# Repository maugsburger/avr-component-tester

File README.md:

avr-component-tester
====================

Board zu http://www.mikrocontroller.net/articles/AVR_Transistortester

* Schaltplan: https://raw.github.com/maugsburger/avr-component-tester/master/tester_sheet1.png
* Platinenvorderseite: https://raw.github.com/maugsburger/avr-component-tester/master/tester_top.png
* Platinenrückseite: https://raw.github.com/maugsburger/avr-component-tester/master/tester_bot.png
* Bauteilliste: https://raw.github.com/maugsburger/avr-component-tester/master/bom.txt

## Features

* Zweiter Spannungsregler für unsaubere Verbraucher
    * DC/DC-Wandler für Zenerdiodentest bis 30V
    * PWM-geregelte LCD-Hintergrundbeleuchtung

* Passt in Strapubox 6000

## Lizenz
<br />This work is licensed under a <a rel="license" href="http://creativecommons.org/licenses/by-sa/4.0/">Creative Commons Attribution-ShareAlike 4.0 International License</a>.

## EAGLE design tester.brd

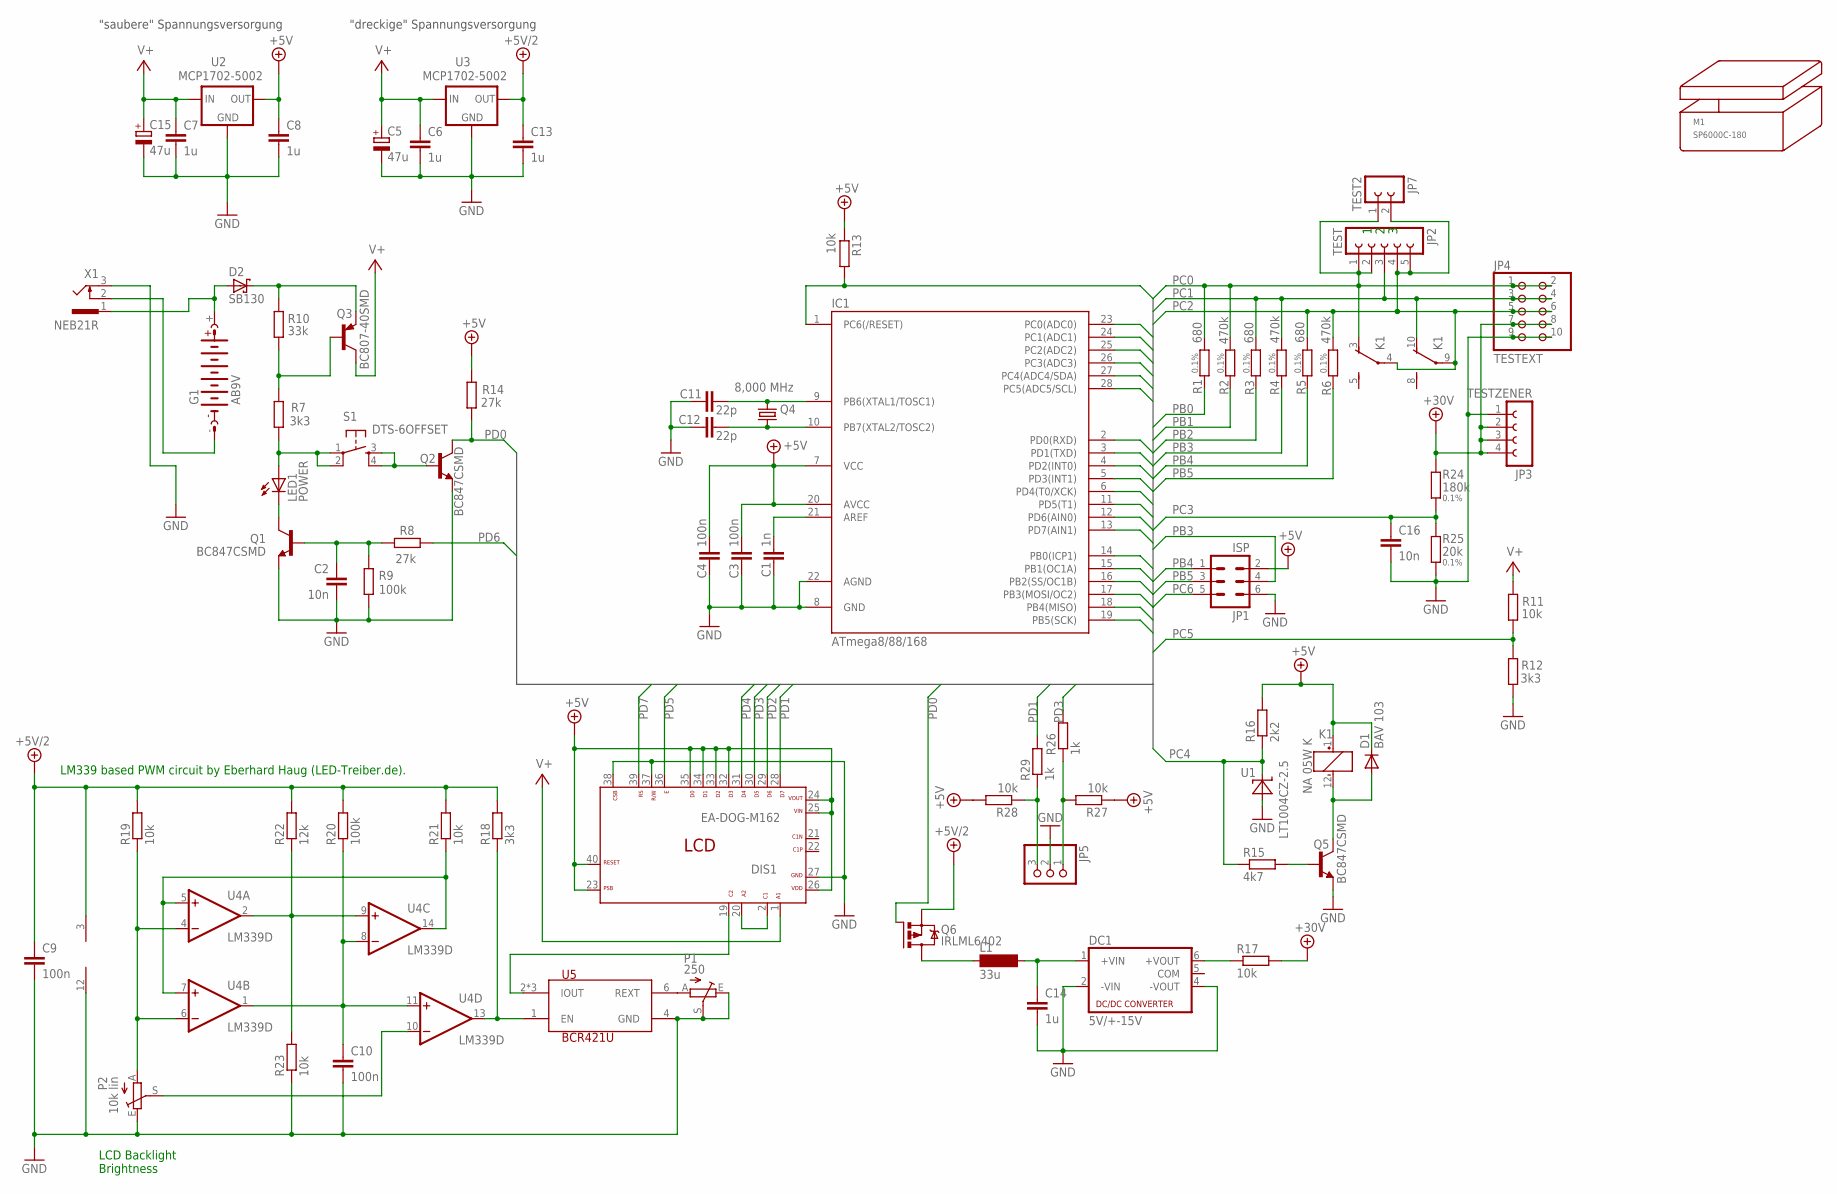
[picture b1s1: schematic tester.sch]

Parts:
C1: 1n; C0805
C2, C16: 10n; C0805
C3, C4, C9, C10: 100n; C0805
C5, C15: 47u; 153CLV-0505
C6, C7, C8, C13, C14: 1u; C0805
C11, C12: 22p; C0805
D1: BAV 103; SOD80C
D2: SB130; DIODE-3-5A-V
DC1: 5V/+-15V; NMA
DIS1: EA-DOG-M162; EA_DOGM
G1: AB9V
IC1: ATmega8/88/168; DIL28-3
JP1: ISP; ML6
JP2: TEST; FE05-1
JP3: TESTZENER; FE04-1
JP4: TESTEXT; 2X05
JP5: PINHD-1X3; 1X03
JP7: TEST2; FE02-1
K1: NA 05W K; NA
L1: 33u; SM-NE29-B
LED1: POWER; LED5MM
M1: SP6000C-180
P1: 250; CA6H
P2: 10k lin; CA9V
Q1, Q2, Q5: BC847CSMD; SOT23
Q3: BC807-40SMD; SOT23-BEC
Q4: 8,000 MHz; HC49/S
Q6: IRLML6402; MICRO3
R1, R3, R5: 680; R0805; TOLERANCE 0.1%
R2, R4, R6: 470k; R0805; TOLERANCE 0.1%
R7, R12, R18: 3k3; R0805
R8, R14: 27k; R0805
R9, R20: 100k; R0805
R10: 33k; R0805
R11, R13, R17, R19, R21, R23, R27, R28: 10k; R0805
R15: 4k7; R0805
R16: 2k2; R0805
R22: 12k; R0805
R24: 180k; R0805; TOLERANCE 0.1%
R25: 20k; R0805; TOLERANCE 0.1%
R26, R29: 1k; R0805
S1: DTS-6OFFSET; DTS-6S
U1: LT1004CZ-2.5; TO92
U2, U3: MCP1702-5002; TO92-LOWDROP
U4: LM339D; SO14
U5: BCR421U; SC74_INFINEON
X1: NEB21R

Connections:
+5V: C3.2, C4.1, C8.1, D1.C, DIS1.23, DIS1.24, DIS1.25, DIS1.26, DIS1.32, DIS1.33, DIS1.34, DIS1.35, DIS1.40, IC1.7 (VCC), IC1.20 (AVCC), JP1.2, K1.1 (+), R13.1, R14.2, R16.2, R27.1, R28.2, U2.OUT
+5V/2: C9.1, C13.1, Q6.2 (S), R18.2, R19.2, R20.2, R21.2, R22.2, U3.OUT, U4.3 (V+)
+30V: JP3.2, JP3.3, JP3.4, JP4.7, JP4.8, R17.2, R24.2
AREF: C1.2, IC1.21 (AREF)
GND: C1.1, C2.2, C3.1, C4.2, C5.-, C6.2, C7.2, C8.2, C9.2, C10.2, C11.1, C12.1, C13.2, C14.2, C15.-, C16.2, DC1.2 (-VIN), DC1.4 (-VOUT), DIS1.27, DIS1.37, DIS1.38, IC1.8 (GND), IC1.22 (AGND), JP1.6, JP3.1, JP4.9, JP4.10, JP5.2, P1.E, P1.S, P2.E, Q1.2 (E), Q2.2 (E), Q5.2 (E), R9.1, R12.1, R23.1, R25.1, U1.1 (A), U2.GND, U3.GND, U4.12 (GND), U5.4 (GND), X1.3
unnamed: P1.A, U5.6 (REXT)
unnamed: DIS1.2, DIS1.20
unnamed: Q2.1 (B), S1.3, S1.4
unnamed: R22.1, R23.2, U4.2 (OUT), U4.9 (+IN)
unnamed: G1.-, X1.2
unnamed: C10.1, R20.1, U4.1 (OUT), U4.8 (-IN), U4.11 (+IN)
unnamed: R21.1, U4.5 (+IN), U4.7 (+IN), U4.14 (OUT)
unnamed: LED1.K (C), Q1.3 (C)
unnamed: D2.C, Q3.E, R10.1
unnamed: DIS1.19, U5.2 (IOUT), U5.3 (IOUT), U5.5 (IOUT)
unnamed: C11.2, IC1.9 (PB6(XTAL1/TOSC1)), Q4.2
unnamed: C12.2, IC1.10 (PB7(XTAL2/TOSC2)), Q4.1
unnamed: JP5.3, R28.1, R29.1
unnamed: P2.A, R19.1, U4.4 (-IN), U4.6 (-IN)
unnamed: P2.S, U4.10 (-IN)
unnamed: R18.1, U4.13 (OUT), U5.1 (EN)
unnamed: D1.A, K1.12 (-), Q5.3 (C)
unnamed: JP5.1, R26.1, R27.2
unnamed: LED1.A, R7.1, S1.1, S1.2
unnamed: Q5.1 (B), R15.2
unnamed: D2.A, G1.+, X1.1
unnamed: L1.1, Q6.3 (D)
unnamed: C14.1, DC1.1 (+VIN), L1.2
unnamed: DC1.6 (+VOUT), R17.1
unnamed: Q3.B, R7.2, R10.2
unnamed: C2.1, Q1.1 (B), R8.2, R9.2
PB0: IC1.14 (PB0(ICP1)), R1.1
PB1: IC1.15 (PB1(OC1A)), R2.1
PB2: IC1.16 (PB2(SS/OC1B)), R3.1
PB3: IC1.17 (PB3(MOSI/OC2)), JP1.4, R4.1
PB4: IC1.18 (PB4(MISO)), JP1.1, R5.1
PB5: IC1.19 (PB5(SCK)), JP1.3, R6.1
PC0: IC1.23 (PC0(ADC0)), JP2.1, JP2.2, JP4.1, JP4.2, JP7.1, K1.3 (O), R1.2, R2.2
PC1: IC1.24 (PC1(ADC1)), JP2.3, JP4.3, JP4.4, K1.10 (O), R3.2, R4.2
PC2: IC1.25 (PC2(ADC2)), JP2.4, JP2.5, JP4.5, JP4.6, JP7.2, K1.4, K1.9, R5.2, R6.2
PC3: C16.1, IC1.26 (PC3(ADC3)), R24.1, R25.2
PC4: IC1.27 (PC4(ADC4/SDA)), R15.1, R16.1, U1.2 (C)
PC5: IC1.28 (PC5(ADC5/SCL)), R11.2, R12.2
PC6: IC1.1 (PC6(/RESET)), JP1.5, R13.2
PD0: IC1.2 (PD0(RXD)), Q2.3 (C), Q6.1 (G), R14.1
PD1: DIS1.28, IC1.3 (PD1(TXD)), R29.2
PD2: DIS1.29, IC1.4 (PD2(INT0))
PD3: DIS1.30, IC1.5 (PD3(INT1)), R26.2
PD4: DIS1.31, IC1.6 (PD4(T0/XCK))
PD5: DIS1.36, IC1.11 (PD5(T1))
PD6: IC1.12 (PD6(AIN0)), R8.1
PD7: DIS1.39, IC1.13 (PD7(AIN1))
V+: C5.+, C6.1, C7.1, C15.+, DIS1.1, Q3.C, R11.1, U2.IN, U3.IN

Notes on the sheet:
LCD Backlight Brightness
LM339 based PWM circuit by Eberhard Haug (LED-Treiber.de).
"saubere" Spannungsversorgung
"dreckige" Spannungsversorgung

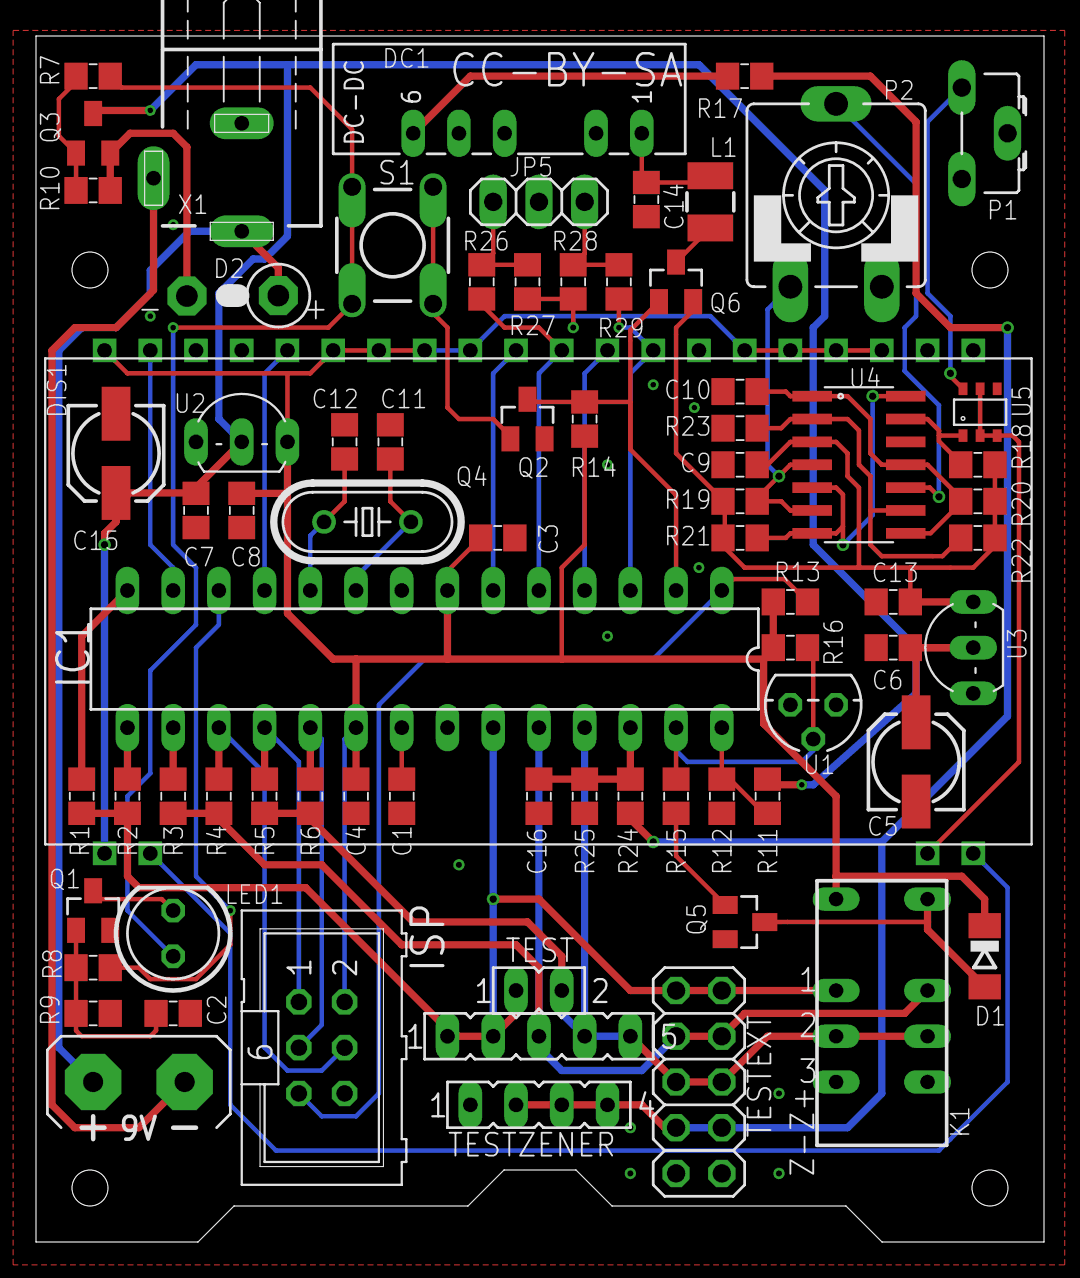
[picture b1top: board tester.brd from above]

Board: 2 copper layers, 56.0 x 67.0 mm, 76 parts (0 on the bottom side), 53 nets.

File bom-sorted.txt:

Stückliste exportiert aus /home/mo/projects/eagle/projects/component tester/tester.sch am 9/4/14 9:58 AM

Qty Value          Device                  Package       Parts                        Description                                                  TOLERANCE
1   NA 05W K       NA                      NA            K1                           RELAY                                                                 
1   BAV 103        DIODE-SOD80C            SOD80C        D1                           DIODE                                                                 
1   AB9V           AB9V                    AB9V          G1                           9-V BATTERY CLIP                                                      
1   BC807-40SMD    BC807-40SMD             SOT23-BEC     Q3                           PNP Transistror                                                       
3   BC847CSMD      BC847CSMD               SOT23         Q1, Q2, Q5                   NPN Transistor                                                        
1   BCR421U        BCR421UHAND             SC74_INFINEON U5                           Constant current source: 10mA (without external resistor).            
2   22p            C-EUC0805               C0805         C11, C12                     CAPACITOR, European symbol                                            
1   1n             C-EUC0805               C0805         C1                           CAPACITOR, European symbol                                            
2   10n            C-EUC0805               C0805         C2, C16                      CAPACITOR, European symbol                                            
4   100n           C-EUC0805               C0805         C3, C4, C9, C10              CAPACITOR, European symbol                                            
5   1u             C-EUC0805               C0805         C6, C7, C8, C13, C14         CAPACITOR, European symbol                                            
2   47u            CPOL-EU153CLV-0505      153CLV-0505   C5, C15                      POLARIZED CAPACITOR, European symbol                                  
1   DTS-6          DTS-6                   DTS-6         S1                                                                                                 
1   EA-DOG-M162    EA-DOG-M_LCD            EA_DOGM       DIS1                                                                                               
1   TEST2          FE02-1                  FE02-1        JP7                          FEMALE HEADER                                                         
1   TESTZENER      FE04-1                  FE04-1        JP3                          FEMALE HEADER                                                         
1   TEST           FE05-1                  FE05-1        JP2                          FEMALE HEADER                                                         
1   IRLML6402      IRLML6402               MICRO3        Q6                           HEXFET P-Channel Power MOSFET                                         
1   POWER          LED5MMEXT               LED5MM        LED1                         LED                                                                   
1   10k lin        TRIM_EU-CA9V            CA9V          P2                           POTENTIOMETER                                                         
1   LT1004CZ-2.5   LM329DZ                 TO92          U1                           National Semiconductor LM329                                          
1   LM339D         LM339D                  SO14          U4                           Low Power Low Offset Voltage Quad Comparators                         
2   MCP1702-5002   MCP1702-5002            TO92-LOWDROP  U2, U3                                                                                             
1   ATmega8/88/168 MEGA8-PU                DIL28-3       IC1                                                                                                
1   8,000 MHz      CRYSTALHC49S            HC49/S        Q4                           CRYSTAL                                                               
1   ISP            ML6                     ML6           JP1                          HARTING                                                               
1   NEB21R         NEB21R                  NEB21R        X1                           Netzgeräte-Einbaukupplung abgewinkelte Ausführung mit Öffner          
1   5V/+-15V       NMA                     NMA           DC1                          DC-DC CONVERTER                                                       
1   TESTEXT        PINHD-2X5               2X05          JP4                          PIN HEADER                                                            
1   33k            R-EU_R0805              R0805         R10                          RESISTOR, European symbol                                             
6   10k            R-EU_R0805              R0805         R11, R13, R17, R19, R21, R23 RESISTOR, European symbol                                             
1   4k7            R-EU_R0805              R0805         R15                          RESISTOR, European symbol                                             
1   2k2            R-EU_R0805              R0805         R16                          RESISTOR, European symbol                                             
1   12k            R-EU_R0805              R0805         R22                          RESISTOR, European symbol                                             
3   3k3            R-EU_R0805              R0805         R7, R12, R18                 RESISTOR, European symbol                                             
2   27k            R-EU_R0805              R0805         R8, R14                      RESISTOR, European symbol                                             
2   100k           R-EU_R0805              R0805         R9, R20                      RESISTOR, European symbol                                             
1   180k           R-EU_R0805              R0805         R24                          RESISTOR, European symbol                                    0.1%     
3   680            R-EU_R0805              R0805         R1, R3, R5                   RESISTOR, European symbol                                    0.1%     
1   20k            R-EU_R0805              R0805         R25                          RESISTOR, European symbol                                    0.1%     
3   470k           R-EU_R0805              R0805         R2, R4, R6                   RESISTOR, European symbol                                    0.1%     
1   SB130          SCHOTTKY-DIODE_RAD3-5-A DIODE-3-5A-V  D2                           Schottky Diode                                                        
1   33u            SM-NE29BIGGERPAD        SM-NE29-B     L1                           INDUCTOR                                                              
1   SP6000C-180    SP6000C-180             SP6000C-180   M1                           Gehäuse Strapubox Typ 6000                                            
1   250            TRIM_EU-CA6H            CA6H          P1                           POTENTIOMETER

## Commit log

2013-04-18 ignore eagle backup files
2013-04-18 readme - projekturl
2013-04-18 history replay r0
2013-04-18 history replay r2
2013-04-18 history replay r3
2013-04-18 history replay r4
2013-04-18 history replay r5
2013-04-18 history replay r6
2013-04-18 history replay r7
2013-04-18 smd-bauteiladapter
2013-04-18 unterschiede zum original
2013-04-18 added licence info on board
2013-06-07 rearranged top mask
2013-06-07 cleaned up some capacitor values, changed P2 to available pinout type
2013-06-10 switched lcd wiring to streifenraster
2013-06-10 power lcd bg led directly from v+
2013-06-10 rearranged some parts, variant without pwm
2013-06-10 smd for q3
2013-06-13 power lcd bg led in series
2013-06-17 adjusted 1702 filter caps
2013-06-17 should know better how to use npn q5
2013-06-18 changed all r/c to 0805, resized some pads, hopefully made easier to solder
2013-07-19 recreate images
2013-07-19 some change
2013-07-19 switch case back, oshpark dru
2013-07-19 silkscreen
2013-07-19 0805 pad size and silk print
2013-07-19 no more c from resistor lib, all rcl now
2013-07-19 more silk screen tuning
2013-07-19 lib fine tuning
2013-07-19 silk screen on pads
2013-07-22 continous part names/numbers
2013-07-22 bill of materials
2013-07-24 local oscillator gnd plane
2013-07-27 eindeutige urls in readme
2013-08-05 fix for reichelt r25 20k .1% n/a => parallel r25 22k and r26 220k
2013-08-05 Revert "fix for reichelt"
    This reverts commit 00bdf40ca26db270fa33158348546dbcbdb5b146.
    Reichelt offers 162K/18K => 1:10-divider
2013-08-08 gerber for dfrobot
2013-08-09 corrected angles
2013-08-09 shrinked
2013-08-27 remove gerber out
2013-09-13 remove obsolete files
2013-10-04 IRLML 6402 for Q6
2013-11-08 combined zif/smd adapter
2013-11-08 dual smd adapter
2013-11-08 change q6, s1
    remove q6 option for irfr9024
    tactile switch s1 instead of pin header
2013-11-12 add silk screen for zif pin usage
2014-09-03 bigger pads for L1
2014-09-03 move ext-header a little bit down
2014-09-03 moved external connector to the left
2014-09-03 move testext silkprint onto pcb
2014-09-03 added bom
2014-09-04 added rotary encoder
2014-09-04 moded resistors below atmel a little bit down
2014-09-04 normal polarity for neb21, gnd is outside
2014-09-09 rotary encoder is PD1 and PD3
2014-11-23 add license

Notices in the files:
tester.brd:
CC-BY-SA
